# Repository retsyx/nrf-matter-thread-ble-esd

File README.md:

# Matter Over Thread End Sleepy Device With BLE Commissioning

Implements a motion sensor with a Nordic nRF52840 or nRF54L15 MCU and a Bosch BMA400 IMU - be notified when the mailman delivers your mail by attaching an accelerometer to the mailbox lid. This code puts together all the bits that seem to be required for a Matter over Thread End Sleepy Device (ESD) with BLE commissioning.

## Power Consumption

Average standby power consumption for both XIAO nRF boards and a BMA400 is measured at approximately 11µA at 4V from the battery. That's an impressive result.

In addition, the XIAO nRF54L15 appears to consume about 30% less power when reporting an event.

## Requirements

* A custom PCB based on the BMA400 and the [XIAO nRF52840](hw/board-nRF52840/) or [XIAO nRF54L15](hw/board-nRF54L15/).
* A LiPo battery with a JST PH 2.0 connector.

Alternatively, you can cobble together your own setup.

## Downloading and Installing the Firmware

Download and unzip the latest released [firmware.zip](https://github.com/retsyx/nrf-matter-thread-ble-esd/releases/latest/download/firmware.zip). It contains firmware for both boards; use the file matching your MCU.

### Installing on the nRF52840

Connect the board by USB and double press its reset button to enter bootloader mode and expose a mountable drive. Copy `nrf52840.uf2` onto the drive. The firmware will immediately start when the copy completes.

### Installing on the nRF54L15

The XIAO nRF54L15 has a built-in CMSIS-DAP debugger accessible over USB. Use [pyOCD](https://pyocd.io/docs/installing.html) 0.42 or newer to program the released `nrf54l15.hex`; no external debugger or Nordic SDK is needed.

Install pyOCD in a Python virtual environment (macOS/Linux commands):

```sh
python3 -m venv .venv-pyocd
source .venv-pyocd/bin/activate
python -m pip install --upgrade 'pyocd>=0.42'
```

On Windows, create the environment with `py -3 -m venv .venv-pyocd`, activate it with `.venv-pyocd\Scripts\Activate.ps1` in PowerShell, then run the same pip command.

On Linux, also install pyOCD's [USB udev rules](https://pyocd.io/docs/installing.html#udev-rules-on-linux) to allow access to the debugger.

Connect the board with a USB data cable. From the directory containing the extracted firmware, run:

```sh
python -m pyocd list
python -m pyocd load --target nrf54l --erase sector -O auto_unlock=false nrf54l15.hex
```

`nrf54l` is pyOCD's built-in target name for the nRF54L15; no device pack is required. If multiple probes are connected, add `--uid PROBE_ID` to the load command, using the XIAO's unique ID from `pyocd list`.

The board resets and starts the firmware after programming. Sector erase updates the application while preserving this firmware's Matter/OpenThread settings; `auto_unlock=false` prevents an automatic full-chip erase if the target is locked. Disconnect USB and power-cycle the board before measuring battery consumption.

## Building

### Dependencies

Nordic's nRF Connect SDK must be installed with Matter support.

```sh
nrfutil install sdk-manager
nrfutil sdk-manager install v3.4.1
```

Start the Nordic shell:

```sh
nrfutil sdk-manager toolchain launch --ncs-version v3.4.1 --shell
```

Use the Nordic SDK's `west` tool to install the Matter ZAP tool:

`west zap-install`

### Build

Start the Nordic shell:

```sh
nrfutil sdk-manager toolchain launch --ncs-version v3.4.1 --shell
```

Then run from this directory:

For nRF52840:

```sh
python3 scripts/build.py --board nrf52840 --zap /path/to/zap-cli
```

For nRF54L15:

```sh
python3 scripts/build.py --board nrf54l15 --zap /path/to/zap-cli
```

Alternatively, set `ZAP_CLI` to the executable path or make `zap-cli` available
on `PATH`; then omit `--zap`. An explicit `--zap` takes precedence over `ZAP_CLI`,
which takes precedence over `PATH` discovery.

Use the `--pristine` flag for a clean rebuild, including the first build after
replacing an older SDK. The scripts require NCS 3.4.1 and its matching toolchain.

Local builds generate custom Matter pairing credentials on the first build and
reuse them on subsequent builds. Each board family saves its credentials and
pairing labels in `provisioning/<board>/`, outside the build directory. Console,
battery and `--pristine` builds reuse the same credentials. Open or print
`pairing.png` for a pairing card with a scannable QR code and the human-readable
manual pairing code. Separate `pairing.svg` and `pairing.txt` files are also saved.

The `provisioning/` directory is ignored by Git. Back it up with your device's
pairing label; deleting it causes a future local build to create new credentials.
Changing firmware credentials on an already paired device requires a factory
reset before pairing again with the new codes.

For multiple devices, generate a separate credential set for each physical
device and select its `provisioning.json` when building and checking:

```sh
python3 scripts/provision.py --output-dir provisioning/mailbox-01
python3 scripts/build.py --board nrf52840 --provisioning provisioning/mailbox-01/provisioning.json --zap /path/to/zap-cli
python3 scripts/check-build.py --board nrf52840 --provisioning provisioning/mailbox-01/provisioning.json
```

The generator accepts optional `--passcode` and `--discriminator` values;
otherwise it chooses random values and a random SPAKE2+ salt, then derives the
matching verifier. Reusing a directory preserves its credentials and regenerates
the pairing card and any missing labels, including for existing credential sets;
conflicting values or a corrupt manifest fail without replacing
the saved identity. Discriminators are limited to 1–4095 because the SDK's current
provider treats zero as an unset value. Run in the Nordic shell; the generator
requires `qrcode`, `cryptography` and Pillow, can select the installed SDK Python
automatically, and installs no packages.

It is possible to specify all the paths to the script, for example:

```sh
python3 scripts/build.py --board nrf52840 --pristine --sdk /path/to/ncs/v3.4.1 --toolchain /path/to/nordic-toolchain --zap /path/to/zap-cli
```

Alternatively, the environment variables
`NCS_SDK_ROOT` and `NCS_TOOLCHAIN_ROOT` can be used.

### Additional Build Parameters

* `--console` enables the UART shell and Thread CLI for diagnostics.
* `--battery` explicitly declares that a rechargeable LiPo is fitted; otherwise battery voltage/percentage remain unknown, even if USB produces charger voltage.
* `--provisioning PATH` selects an existing custom `provisioning.json` and its pairing labels.
* `--default-provisioning` explicitly selects the published development codes. Pass the same provisioning option to `scripts/check-build.py` and `scripts/flash.py`; with no option they check the local board family's saved credentials.

### CI and Releases

GitHub Actions runs the driver tests and builds both MCU variants on every branch push and pull request, or when started manually. Builds use `--default-provisioning` with USB and console disabled. The build checker verifies the published passcode, discriminator, salt and verifier in both Kconfig and compiled headers. Download each board's firmware from the workflow run's artifacts.

Pushing a `v*` tag builds both variants and publishes a GitHub release with `firmware.zip` and a `SHA256SUMS` file for the archive. The ZIP includes HEX/ELF files for both boards, the nRF52840 UF2, installation instructions, version/build information, and checksums. Tags containing a hyphen, such as `v1.1.0-rc.1`, create prereleases. Update `VERSION` before tagging when changing the firmware version.

## Matter Commissioning

An uncommissioned boot opens BLE commissioning for 15 minutes. Add the accessory using a Matter controller and Thread border router.

With your favorite Matter commissioner (HomeKit, etc.) add the accessory.

For a local build, scan its saved `pairing.png` card or enter the manual code
printed on it (`pairing.svg` and `pairing.txt` are also available). Custom pairing
codes change commissioning credentials; the firmware still uses the SDK's
development device-attestation credentials.

GitHub builds and releases retain the existing development credentials and use
the QR code below:

Commissioning values use the defaults:

| Development credential | Value |
| --- | --- |
| Manual code | `34970112332` |
| QR payload | `MT:4CT9142C00KA0648G00` |
| Setup passcode | `20202021` |
| Discriminator | `3840` / `0xF00` |
| Vendor / product | `0xFFF1` / `0x8004` |

### Factory reset

Hold **SW1 for five seconds**, then release it. The firmware erases all existing
Matter pairings (fabrics), Matter operational settings and the saved Thread
network, then reboots and opens its 15-minute BLE pairing window. The provisioned
passcode, discriminator, salt and verifier remain unchanged, so the same QR or
manual pairing code works again. A shorter press cancels the reset. If SW1 is
held during boot, release it before starting a new hold.

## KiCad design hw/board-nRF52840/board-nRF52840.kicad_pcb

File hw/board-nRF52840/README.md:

# XIAO nRF52840 direct-SMD carrier

Standalone **22 × 38 mm, two-layer** KiCad project for the standard XIAO nRF52840. U1 solders directly on fourteen edge lands plus its underside battery pair, **19 BAT+ / 20 GND**. Use the matching `nrf52840` firmware build. The other MCU needs its own carrier.

- Editable [project](board-nRF52840.kicad_pro), [schematic](board-nRF52840.kicad_sch), [routed PCB](board-nRF52840.kicad_pcb) and [custom design rules](board-nRF52840.kicad_dru).
- Purchase from the [parts catalog](parts.json); assemble two front SMD placements (U1/SW1), six back SMD placements (U2, R1/R2, C1-C3), and manual through-hole J1. The local purchasing BOM export (`bom.csv`) is ignored by Git.
- Generate Gerbers, PTH/NPTH drill files and maps, and front/back SMD placement data using the commands below. Local fabrication packages, BOM exports and checksums under `fabrication/` are ignored by Git.
- Review contact positions, copper keepouts and probe access in [geometry](geometry.json). Local [footprints](Board.pretty/), [symbols](board.kicad_sym), [datasheets](datasheets/) and [STEP models](3dmodels/) accompany the project.

H1/H2 and H7/H8 are four 2.2 mm M2 mounting holes at (52,85), (68,85), (52,53), and (68,53) mm. The 16 × 32 mm corner support pattern surrounds the board center; both copper layers and their fills stay outside each mounting hole’s 2.45 mm screw-head clearance. H3–H6 provide mask-only NPTH access to module SWDIO/SWCLK/RESET/GND; backside TP1 is 3V3 reference and TP2 GND. These features add no purchased parts. J1 is **pin 1 GND, pin 2 VBAT**; verify battery plug polarity.

**SW1 factory reset:** hold the top-actuated button for 5 seconds to erase Matter/Thread user state and reboot ready for pairing with the same provisioned Matter credentials. SW1 connects D0 (P0.02) to GND and uses the firmware internal pull-up; its released contact is open. It sits above the module between the two USB-end mounting holes, outside the antenna keepout. The module RESET probe contact is separate and only resets the MCU. See [switch datasheet](datasheets/omron-b3u.pdf) and [geometry](geometry.json) for the footprint and placement.

The locally generated module STEP shows only the official bare PCB core, with a nominal 0.1 mm solder gap. Module electronics, antenna and USB solids are omitted. Regenerate this model after a fresh checkout using the [model provenance and reproduction notes](3dmodels/README.md).

Revision C reduces the carrier to 22 × 38 mm and centers U2/BMA400 at (60,69) mm on the back. U1 is rotated 90° at (59.5,69) mm on the front, centered along the board length while retaining side-edge USB access and the complete antenna and probe-contact keepouts. H7/H8 support the opposite end of the board from H1/H2, and all tracks avoid right-angle joins, including branches. The board passed KiCad 10.0.6 ERC and DRC with zero violations, zero unconnected items and zero schematic-parity issues on 2026-10-20.

Open the project in KiCad 10.0.6. The editable design has not been fabricated or assembled. The custom rules allow the intentional H3–H6 probe holes inside U1's front courtyard; other clearance checks remain active.

Use KiCad's schematic and PCB editors for design changes. The installed [KiCad CLI](https://docs.kicad.org/10.0/en/cli/cli.html) can check and export the current files. Run these commands from the repository root; fresh output goes to a separate temporary directory.

```sh
kicad_cli=/Applications/KiCad/KiCad.app/Contents/MacOS/kicad-cli
xiao_board=hw/board-nRF52840
xiao_out=/tmp/xiao-nrf52840-export
mkdir -p "$xiao_out"
"$kicad_cli" sch erc --severity-all --exit-code-violations --output "$xiao_out/erc.rpt" "$xiao_board/board-nRF52840.kicad_sch"
"$kicad_cli" pcb drc --severity-all --schematic-parity --exit-code-violations --output "$xiao_out/drc.rpt" "$xiao_board/board-nRF52840.kicad_pcb"
```

Run the geometric and trace-angle audit from the repository root with `python3 scripts/check-pcb-layout.py hw/board-nRF52840/board-nRF52840.kicad_pcb`. It checks the centered BMA400, four mounting holes opposing each other around the center, and all perpendicular copper joins.

Review any ERC/DRC violations before exporting manufacturing files. In the same shell:

```sh
"$kicad_cli" sch export pdf --output "$xiao_out/schematic.pdf" "$xiao_board/board-nRF52840.kicad_sch"
"$kicad_cli" pcb export gerbers --layers "F.Cu,B.Cu,F.Mask,B.Mask,F.Paste,B.Paste,F.Silkscreen,B.Silkscreen,Edge.Cuts" --no-protel-ext --use-drill-file-origin --subtract-soldermask --output "$xiao_out/gerbers/" "$xiao_board/board-nRF52840.kicad_pcb"
"$kicad_cli" pcb export drill --format excellon --drill-origin plot --excellon-separate-th --generate-map --generate-report --output "$xiao_out/gerbers/" "$xiao_board/board-nRF52840.kicad_pcb"
"$kicad_cli" pcb export pos --format csv --side front --units mm --smd-only --exclude-fp-th --exclude-dnp --use-drill-file-origin --output "$xiao_out/front-smd.csv" "$xiao_board/board-nRF52840.kicad_pcb"
"$kicad_cli" pcb export pos --format csv --side back --units mm --smd-only --exclude-fp-th --exclude-dnp --use-drill-file-origin --output "$xiao_out/back-smd.csv" "$xiao_board/board-nRF52840.kicad_pcb"
```

After design changes, update the parts catalog, export a local purchasing BOM, package the fresh manufacturing files, and recompute the fabrication checksums.

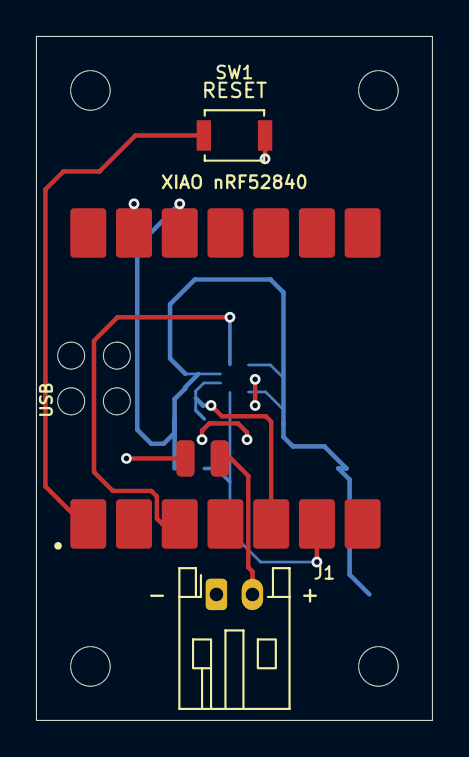
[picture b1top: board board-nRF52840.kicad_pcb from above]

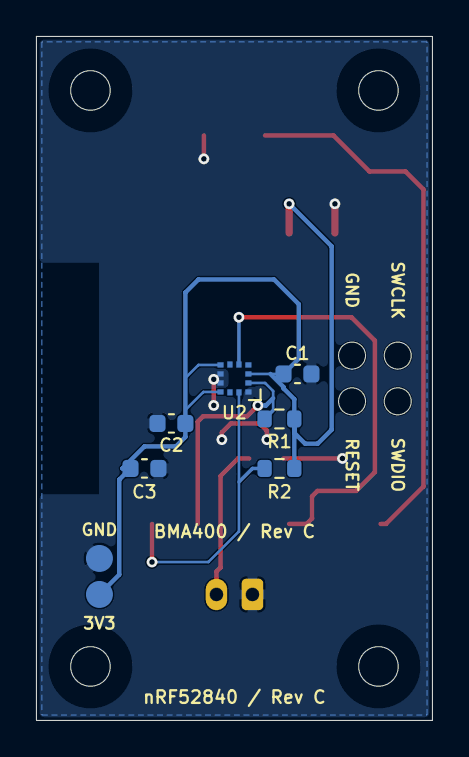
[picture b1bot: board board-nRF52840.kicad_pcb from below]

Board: 2 copper layers, 22.0 x 38.0 mm, 19 parts (8 on the bottom side), 7 nets.

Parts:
C1, C2: 100nF; C_0603_1608Metric
C3: 1uF; C_0603_1608Metric
H1, H2, H7, H8: MountingHole_2.2mm_M2
H3: SWDIO probe access; ProbeAccess_Hole_1.5mm
H4: SWCLK probe access; ProbeAccess_Hole_1.5mm
H5: RESET probe access; ProbeAccess_Hole_1.5mm
H6: GND probe access; ProbeAccess_Hole_1.5mm
J1: JST-PH 2.0 / BATTERY; JST_PH_S2B-PH-K_1x02_P2.00mm_Horizontal
R1, R2: 10k; R_0603_1608Metric
SW1: B3U-1000P; SW_SPST_B3U-1000P
TP1: +3V3; TestPoint_Pad_D1.5mm
TP2: GND; TestPoint_Pad_D1.5mm
U1: XIAO nRF52840; XIAO_nRF52840_SMD
U2: BMA400; LGA-12_2x2mm_P0.5mm

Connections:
/+3V3: C1.1, C2.1, C3.1, R1.1, R2.1, TP1.1, U1.12, U2.3, U2.7, U2.10
/ACC_INT1: U1.3, U2.5
/FACTORY_RESET: SW1.1, U1.1
/GND: C1.2, C2.2, C3.2, J1.1, SW1.2, TP2.1, U1.13, U1.20, U2.1, U2.8, U2.9
/I2C_SCL: R2.2, U1.6, U2.12
/I2C_SDA: R1.2, U1.5, U2.2
/VBAT: J1.2, U1.19
